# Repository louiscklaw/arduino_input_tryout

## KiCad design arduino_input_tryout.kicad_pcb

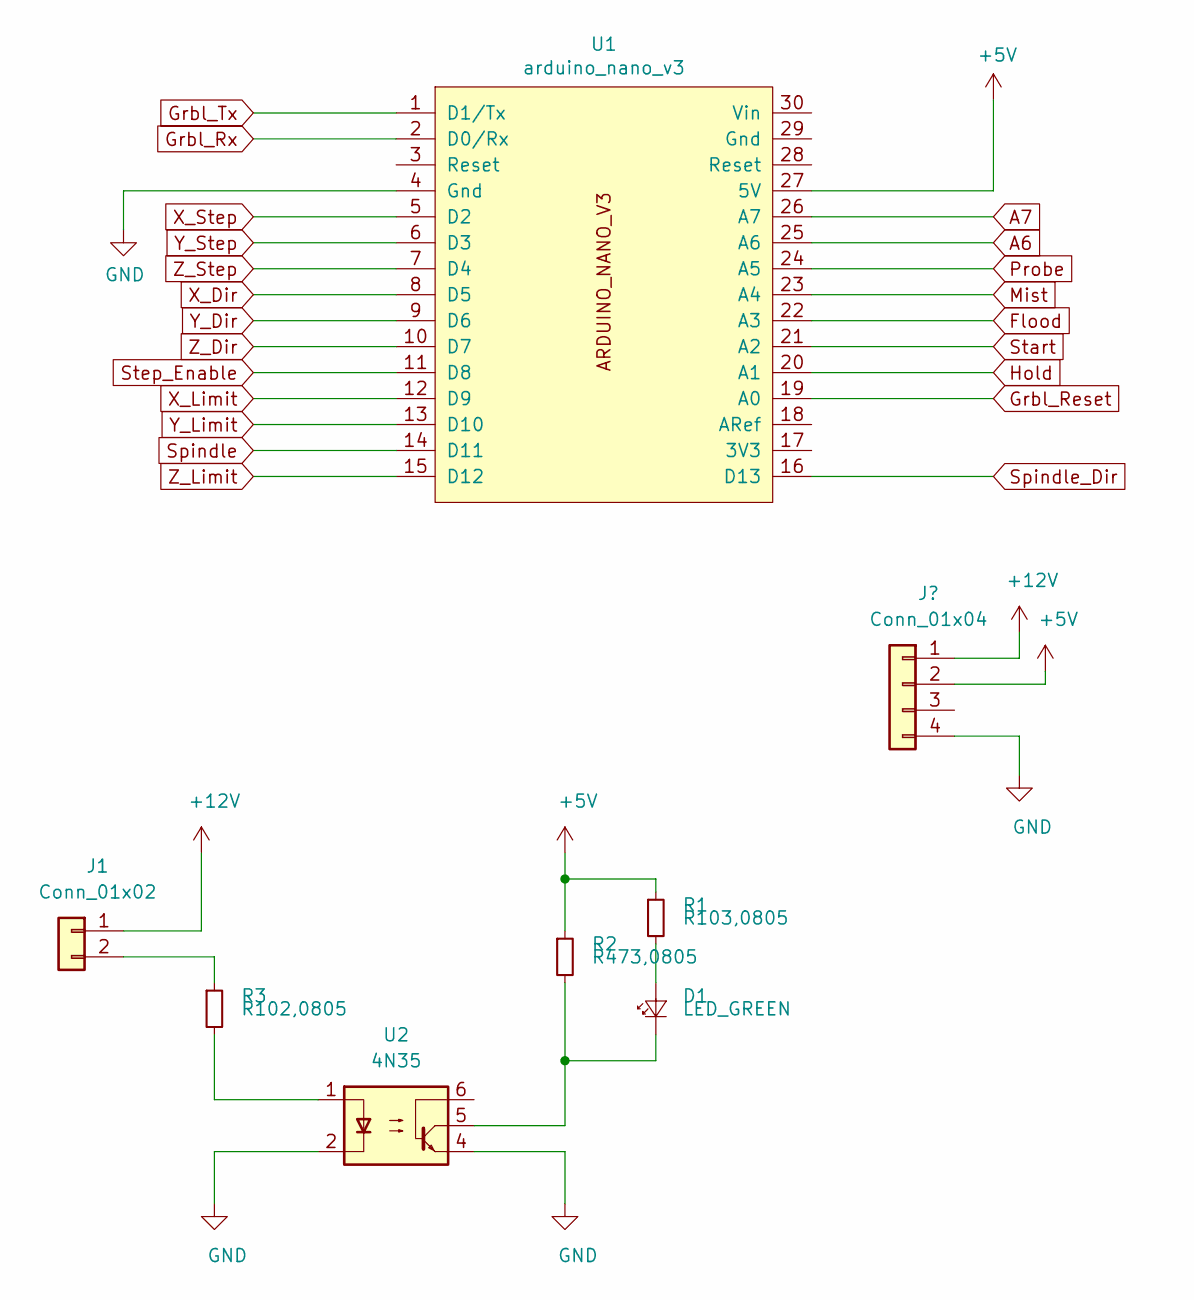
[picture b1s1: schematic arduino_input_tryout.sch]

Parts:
D1: LED_GREEN; LED_0805_2012Metric_Pad1.15x1.40mm_HandSolder
J1: Conn_01x02; PinHeader_1x02_P2.54mm_Vertical
R1: R103,0805; R_0805_2012Metric_Pad1.15x1.40mm_HandSolder
R2: R473,0805; R_0805_2012Metric_Pad1.15x1.40mm_HandSolder
R3: R102,0805; R_0805_2012Metric_Pad1.15x1.40mm_HandSolder
U1: arduino_nano_v3; Arduino_Nano
U2: 4N35; DIP-6_W7.62mm

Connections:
+5V: R1.1, R2.1, U1.27 (5V); also elsewhere on the board
+12V: J1.1; also elsewhere on the board
A6: U1.25 (A6)
A7: U1.26 (A7)
Flood: U1.22 (A3)
GND: U1.4 (Gnd), U2.2, U2.4; also elsewhere on the board
Grbl_Reset: U1.19 (A0)
Grbl_Rx: U1.2 (D0/Rx)
Grbl_Tx: U1.1 (D1/Tx)
Hold: U1.20 (A1)
Mist: U1.23 (A4)
unnamed: D1.1 (K), R2.2, U2.5
unnamed: D1.2 (A), R1.2
unnamed: J1.2, R3.1
unnamed: R3.2, U2.1
Probe: U1.24 (A5)
Spindle: U1.14 (D11)
Spindle_Dir: U1.16 (D13)
Start: U1.21 (A2)
Step_Enable: U1.11 (D8)
X_Dir: U1.8 (D5)
X_Limit: U1.12 (D9)
X_Step: U1.5 (D2)
Y_Dir: U1.9 (D6)
Y_Limit: U1.13 (D10)
Y_Step: U1.6 (D3)
Z_Dir: U1.10 (D7)
Z_Limit: U1.15 (D12)
Z_Step: U1.7 (D4)

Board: 2 copper layers, 8 parts (0 on the bottom side), 7 nets, no tracks yet.

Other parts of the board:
J2: Conn_01x04; PinHeader_1x04_P2.54mm_Vertical

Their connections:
+5V: J2.2; also elsewhere on the board
+12V: J2.1; also elsewhere on the board
GND: J2.4; also elsewhere on the board

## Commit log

2018-12-04 update,
2020-05-05 ci: init travis build config,
2020-05-05 ci: init travis token,
